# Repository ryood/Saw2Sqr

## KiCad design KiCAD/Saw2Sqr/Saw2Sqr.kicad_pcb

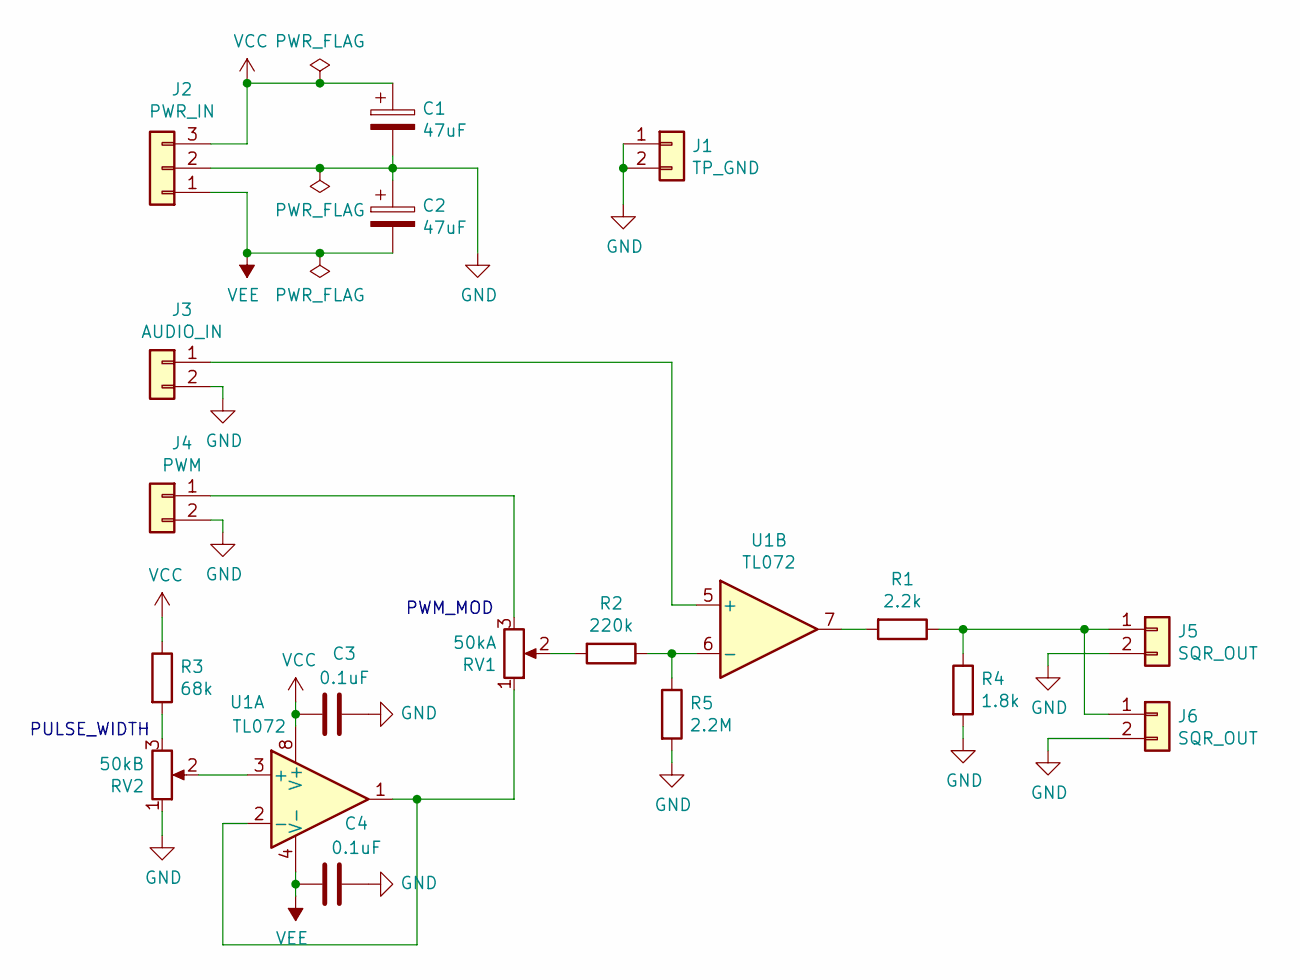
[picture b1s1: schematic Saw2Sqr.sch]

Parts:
C1, C2: 47uF; CP_Radial_D5.0mm_P2.50mm
C3, C4: 0.1uF; C_Disc_D3.0mm_W1.6mm_P2.50mm
J1: TP_GND; PinHeader_1x02_P2.54mm_Vertical
J2: PWR_IN; PinHeader_1x03_P2.54mm_Horizontal
J3: AUDIO_IN; PinHeader_1x02_P2.54mm_Horizontal
J4: PWM; JST_XH_B2B-XH-A_1x02_P2.50mm_Vertical
J5, J6: SQR_OUT; JST_XH_B2B-XH-A_1x02_P2.50mm_Vertical
R1: 2.2k; R_Axial_DIN0207_L6.3mm_D2.5mm_P7.62mm_Horizontal
R2: 220k; R_Axial_DIN0207_L6.3mm_D2.5mm_P7.62mm_Horizontal
R3: 68k; R_Axial_DIN0207_L6.3mm_D2.5mm_P7.62mm_Horizontal
R4: 1.8k; R_Axial_DIN0207_L6.3mm_D2.5mm_P7.62mm_Horizontal
R5: 2.2M; R_Axial_DIN0207_L6.3mm_D2.5mm_P7.62mm_Horizontal
RV1: 50kA; Potentiometer_Alps_RK097_Single_Horizontal
RV2: 50kB; Potentiometer_Alps_RK097_Single_Horizontal
U1: TL072; DIP-8_W7.62mm_Socket

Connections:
GND: C1.2, C2.1, C3.1, C4.2, J1.1, J1.2, J2.2, J3.2, J4.2, J5.2, J6.2, R4.2, R5.2, RV2.1
unnamed: J3.1, U1.5 (+)
unnamed: J4.1, RV1.3
unnamed: J5.1, J6.1, R1.1, R4.1
unnamed: R1.2, U1.7
unnamed: R2.1, R5.1, U1.6 (-)
unnamed: R2.2, RV1.2
unnamed: R3.2, RV2.3
unnamed: RV1.1, U1.1, U1.2 (-)
unnamed: RV2.2, U1.3 (+)
VCC: C1.1, C3.2, J2.3, R3.1, U1.8 (V+)
VEE: C2.2, C4.1, J2.1, U1.4 (V-)

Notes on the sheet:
PULSE_WIDTH
PWM_MOD

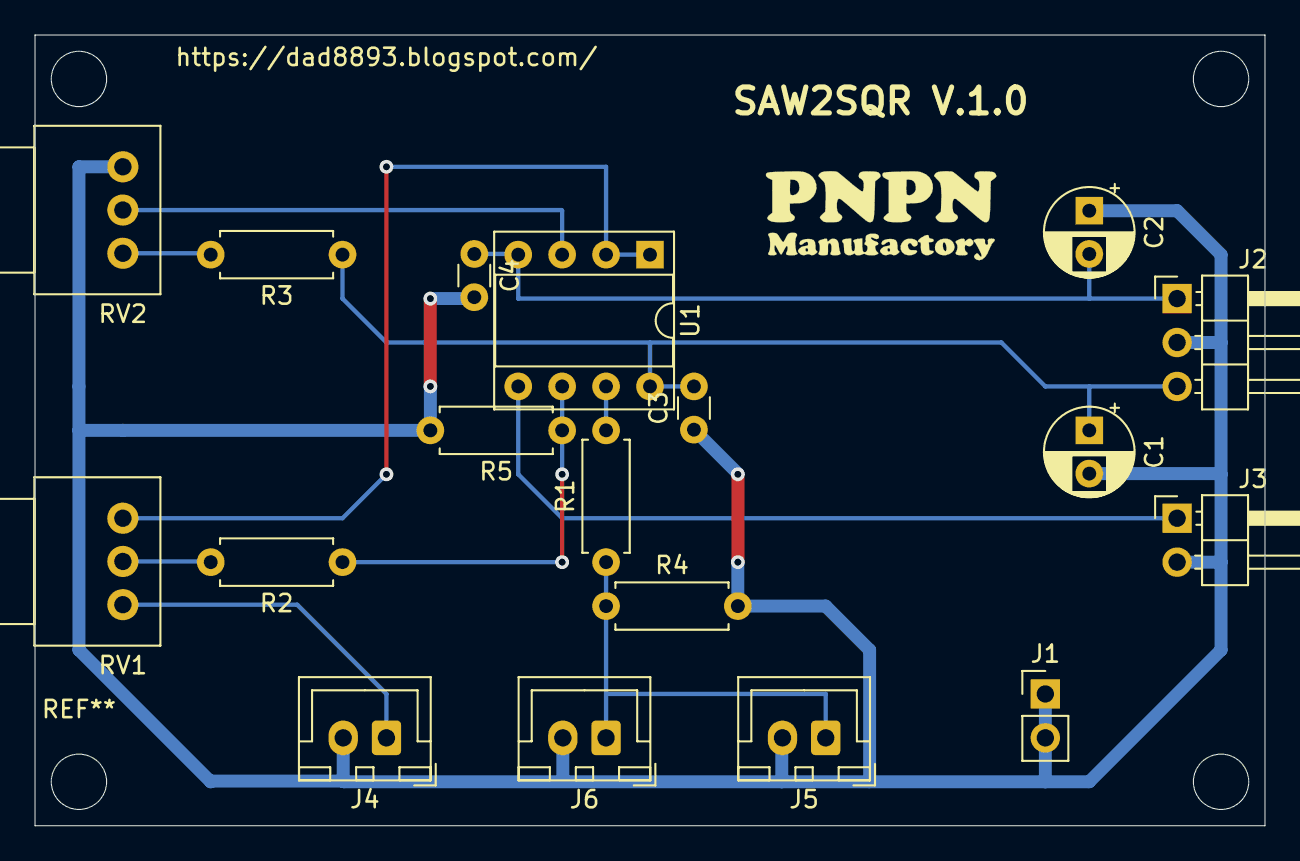
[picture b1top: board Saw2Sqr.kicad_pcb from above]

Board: 2 copper layers, 71.1 x 45.7 mm, 18 parts (0 on the bottom side), 12 nets.

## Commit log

2021-04-25 Panel mount
